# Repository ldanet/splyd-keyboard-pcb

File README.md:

# Splyd Keyboard PCB

Kicad files for my custom split ergo keyboard PCB.

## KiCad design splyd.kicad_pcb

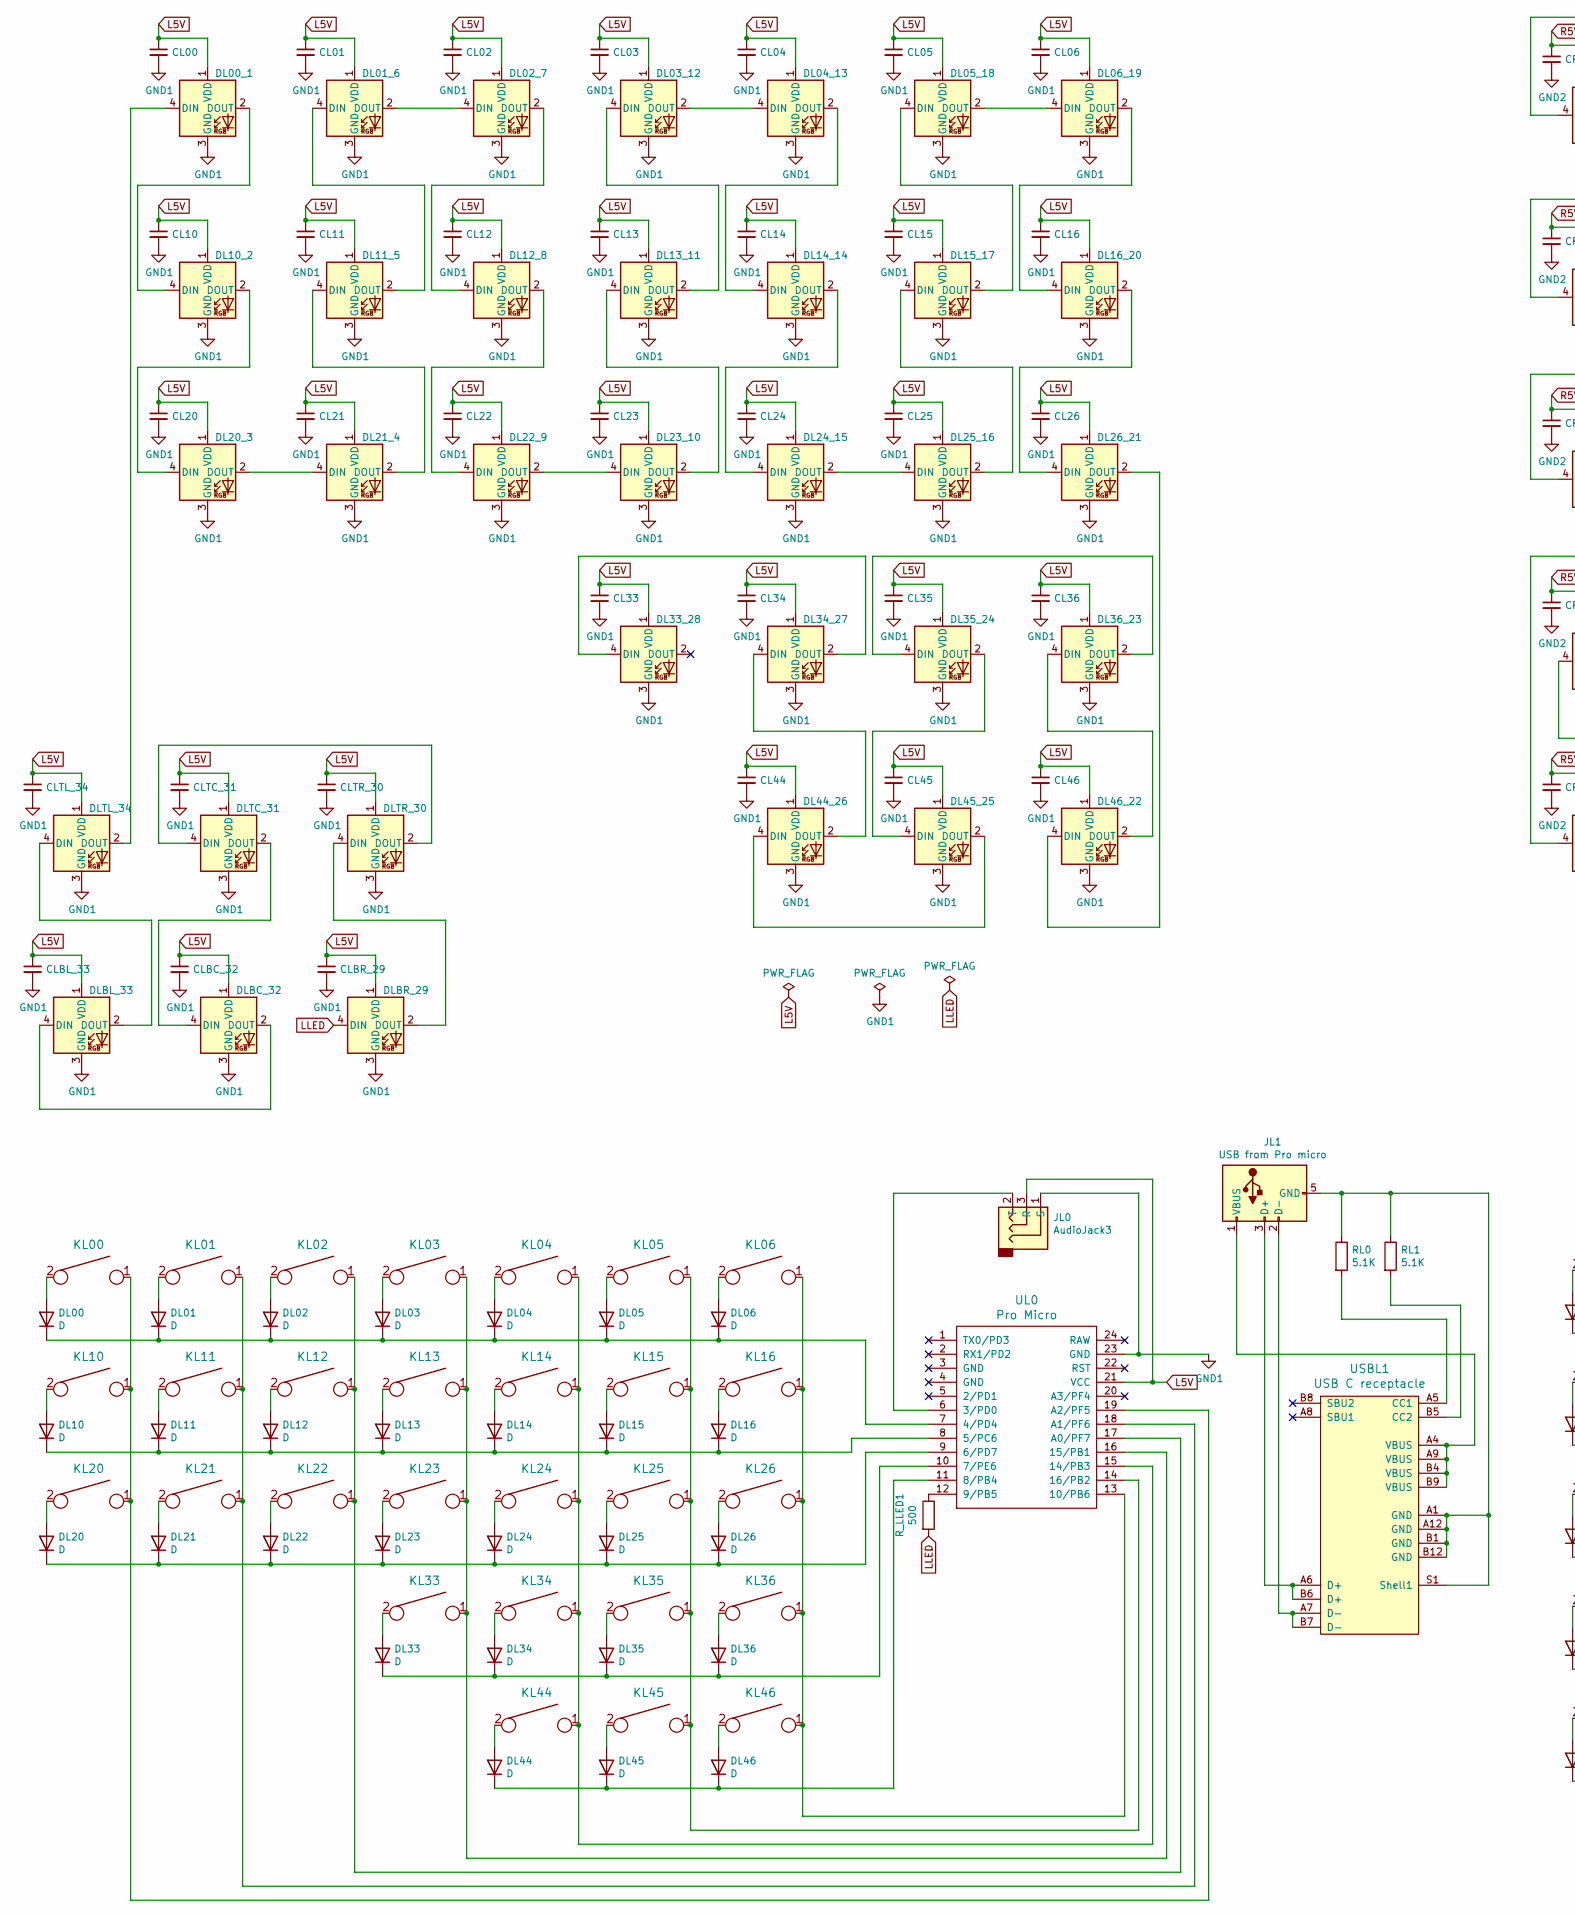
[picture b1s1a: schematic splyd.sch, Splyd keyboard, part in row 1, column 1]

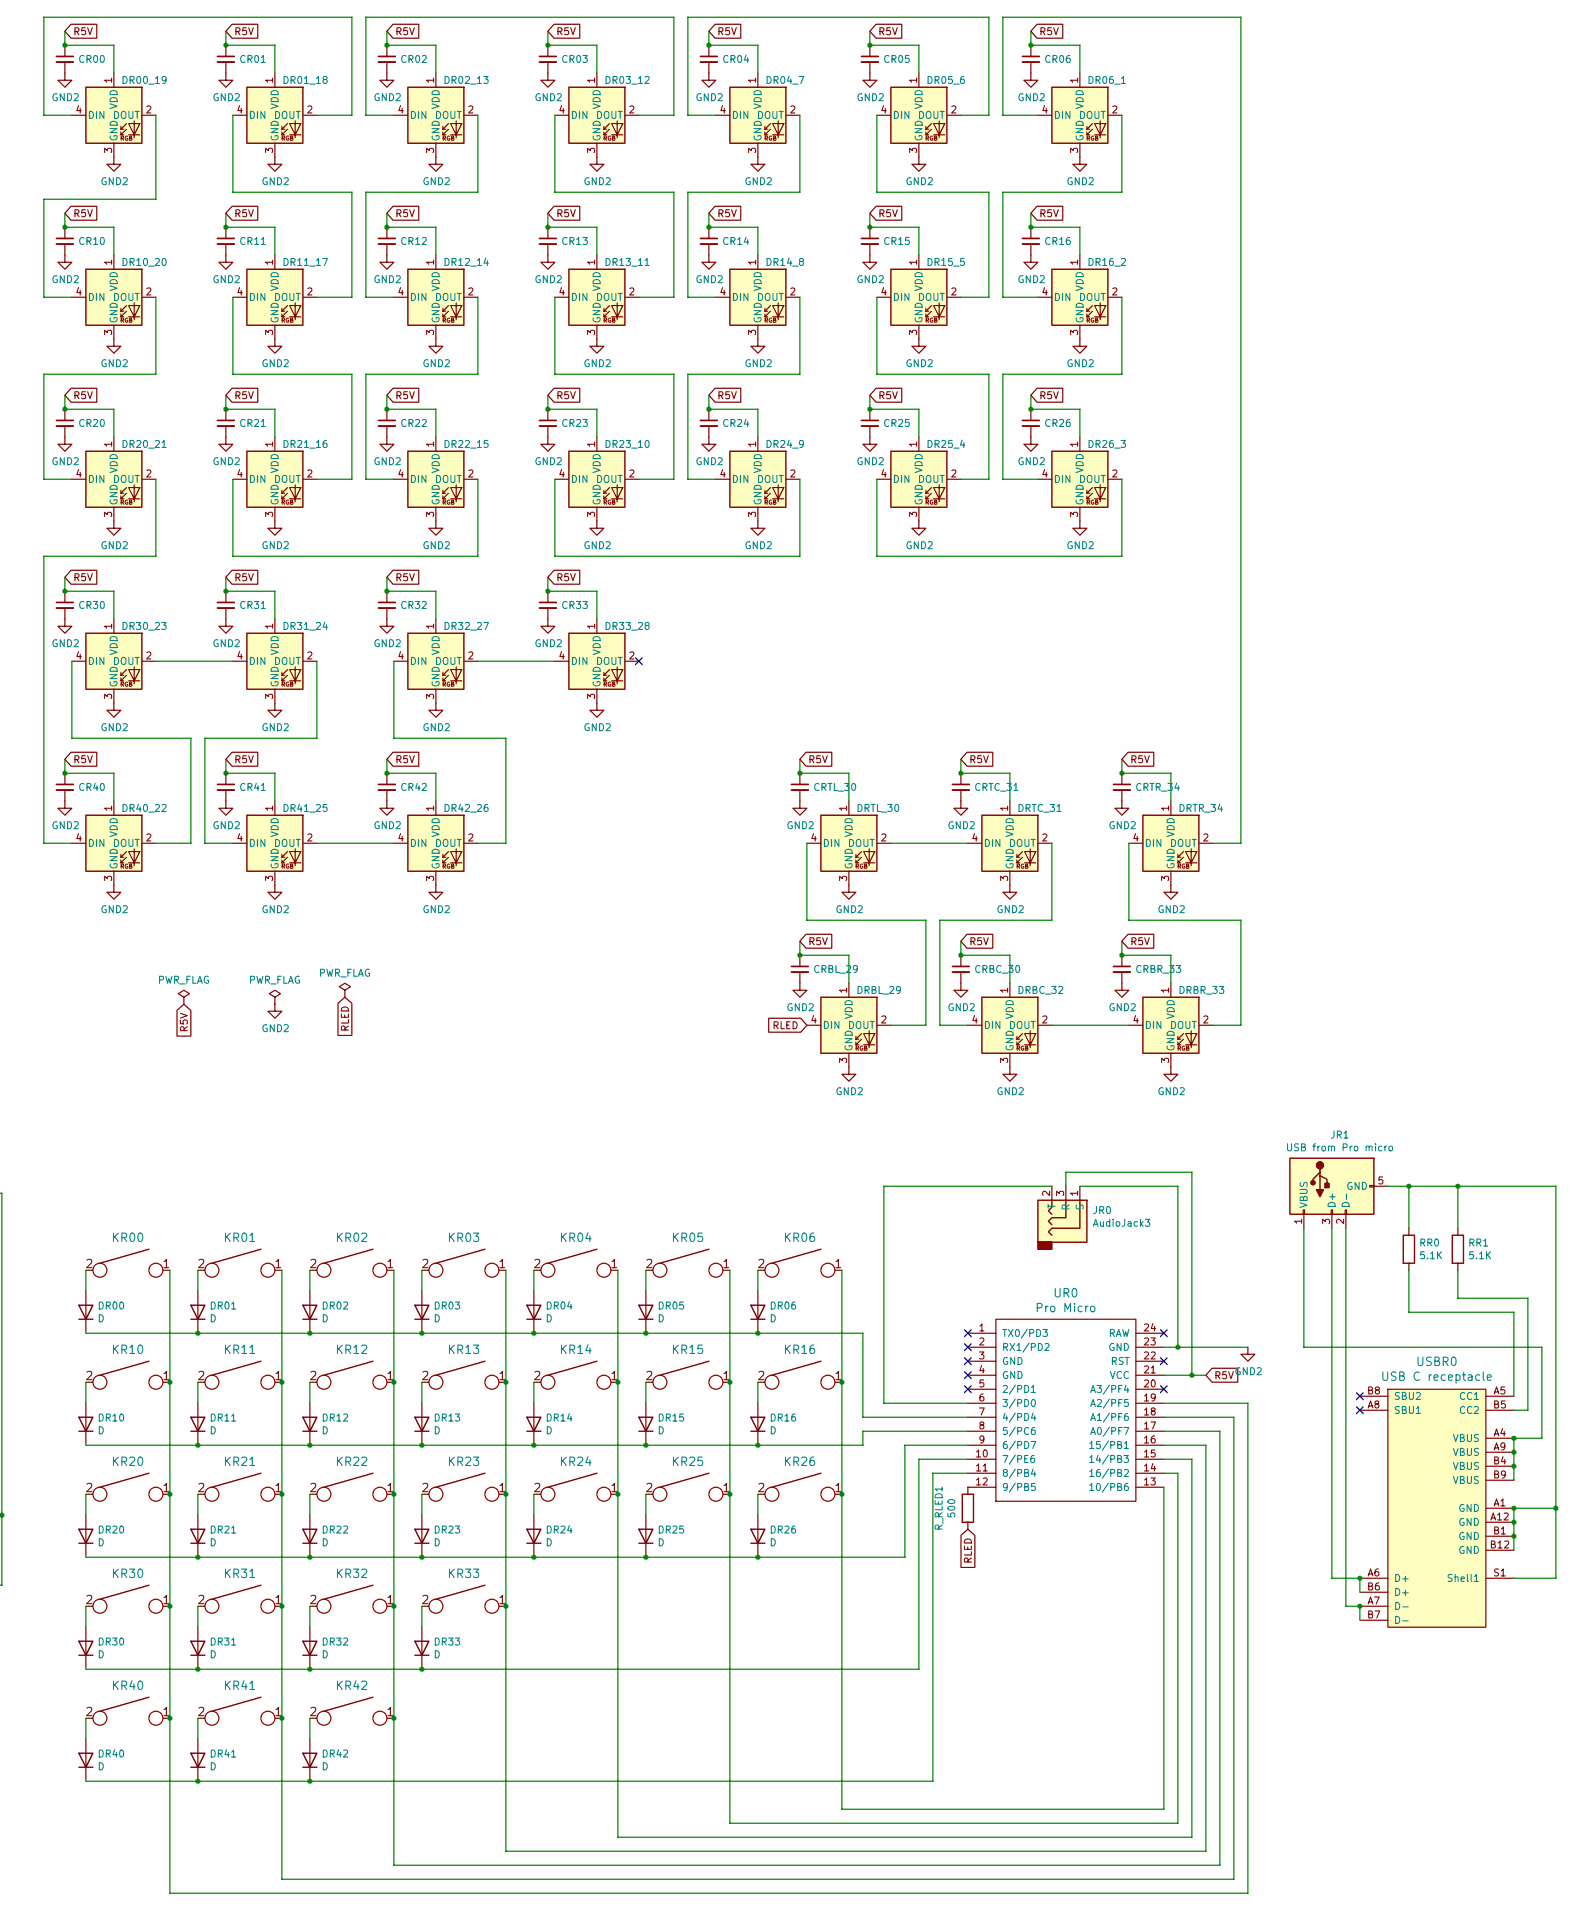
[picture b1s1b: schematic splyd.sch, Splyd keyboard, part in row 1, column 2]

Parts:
CL00, CL01, CL02, CL03, CL04, CL05, CL06, CL10, CL11, CL12, CL13, CL14, CL15, CL16, CL20, CL21, CL22, CL23, CL24, CL25, CL26, CL33, CL34, CL35, CL36, CL44, CL45, CL46: C_Small; C_0603_1608Metric_Pad1.05x0.95mm_HandSolder
CLBC_32: C_Small; C_0603_1608Metric_Pad1.05x0.95mm_HandSolder
CLBL_33: C_Small; C_0603_1608Metric_Pad1.05x0.95mm_HandSolder
CLBR_29: C_Small; C_0603_1608Metric_Pad1.05x0.95mm_HandSolder
CLTC_31: C_Small; C_0603_1608Metric_Pad1.05x0.95mm_HandSolder
CLTL_34: C_Small; C_0603_1608Metric_Pad1.05x0.95mm_HandSolder
CLTR_30: C_Small; C_0603_1608Metric_Pad1.05x0.95mm_HandSolder
CR00, CR01, CR02, CR03, CR04, CR05, CR06, CR10, CR11, CR12, CR13, CR14, CR15, CR16, CR20, CR21, CR22, CR23, CR24, CR25, CR26, CR30, CR31, CR32, CR33, CR40, CR41, CR42: C_Small; C_0603_1608Metric_Pad1.05x0.95mm_HandSolder
CRBC_30: C_Small; C_0603_1608Metric_Pad1.05x0.95mm_HandSolder
CRBL_29: C_Small; C_0603_1608Metric_Pad1.05x0.95mm_HandSolder
CRBR_33: C_Small; C_0603_1608Metric_Pad1.05x0.95mm_HandSolder
CRTC_31: C_Small; C_0603_1608Metric_Pad1.05x0.95mm_HandSolder
CRTL_30: C_Small; C_0603_1608Metric_Pad1.05x0.95mm_HandSolder
CRTR_34: C_Small; C_0603_1608Metric_Pad1.05x0.95mm_HandSolder
DL00, DL01, DL02, DL03, DL04, DL05, DL06, DL10, DL11, DL12, DL13, DL14, DL15, DL16, DL20, DL21, DL22, DL23, DL24, DL25, DL26, DL33, DL34, DL35, DL36, DL44, DL45, DL46: D; D_SOD123_axial
DL00_1, DL01_6, DL02_7, DL03_12, DL04_13, DL05_18, DL06_19, DL10_2, DL11_5, DL12_8, DL13_11, DL14_14, DL15_17, DL16_20, DL20_3, DL21_4, DL22_9, DL23_10, DL24_15, DL25_16, DL26_21, DL33_28, DL34_27, DL35_24, DL36_23, DL44_26, DL45_25, DL46_22: SK6812MINI-E; SK6812MINIE-simple
DLBC_32: SK6812MINI-E; SK6812MINIE-simple_no-hole
DLBL_33: SK6812MINI-E; SK6812MINIE-simple_no-hole
DLBR_29: SK6812MINI-E; SK6812MINIE-simple_no-hole
DLTC_31: SK6812MINI-E; SK6812MINIE-simple_no-hole
DLTL_34: SK6812MINI-E; SK6812MINIE-simple_no-hole
DLTR_30: SK6812MINI-E; SK6812MINIE-simple_no-hole
DR00, DR01, DR02, DR03, DR04, DR05, DR06, DR10, DR11, DR12, DR13, DR14, DR15, DR16, DR20, DR21, DR22, DR23, DR24, DR25, DR26, DR30, DR31, DR32, DR33, DR40, DR41, DR42: D; D_SOD123_axial
DR00_19, DR01_18, DR02_13, DR03_12, DR04_7, DR05_6, DR06_1, DR10_20, DR11_17, DR12_14, DR13_11, DR14_8, DR15_5, DR16_2, DR20_21, DR21_16, DR22_15, DR23_10, DR24_9, DR25_4, DR26_3, DR30_23, DR31_24, DR32_27, DR33_28, DR40_22, DR41_25, DR42_26: SK6812MINI-E; SK6812MINIE-simple
DRBC_32: SK6812MINI-E; SK6812MINIE-simple_no-hole
DRBL_29: SK6812MINI-E; SK6812MINIE-simple_no-hole
DRBR_33: SK6812MINI-E; SK6812MINIE-simple_no-hole
DRTC_31: SK6812MINI-E; SK6812MINIE-simple_no-hole
DRTL_30: SK6812MINI-E; SK6812MINIE-simple_no-hole
DRTR_34: SK6812MINI-E; SK6812MINIE-simple_no-hole
JL0: AudioJack3; TRS-PJ-320B
JL1: USB from Pro micro; Pad_1x04_SMD_1x2mm
JR0: AudioJack3; TRS-PJ-320B
JR1: USB from Pro micro; Pad_1x04_SMD_1x2mm
KL00, KL01, KL02, KL03, KL04, KL05, KL06, KL10, KL11, KL12, KL13, KL14, KL15, KL16, KL20, KL21, KL22, KL23, KL24, KL25, KL26, KL33, KL34, KL35, KL36, KL44, KL45, KL46: KEYSW; Kailh_socket_MX--space
KR00, KR01, KR02, KR03, KR04, KR05, KR06, KR10, KR11, KR12, KR13, KR14, KR15, KR16, KR20, KR21, KR22, KR23, KR24, KR25, KR26, KR30, KR31, KR32, KR33, KR40, KR41, KR42: KEYSW; Kailh_socket_MX--space
RL0, RL1: 5.1K; R_0603_1608Metric
RR0, RR1: 5.1K; R_0603_1608Metric
R_LLED1: 500; R_0603_1608Metric
R_RLED1: 500; R_0603_1608Metric
UL0: Pro Micro; ArduinoProMicro-ZigZag
UR0: Pro Micro; ArduinoProMicro-ZigZag
USBL1: USB C receptacle; USB_C_GCT_USB4085
USBR0: USB C receptacle; USB_C_GCT_USB4085

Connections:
GND1: CL00.2, CL01.2, CL02.2, CL03.2, CL04.2, CL05.2, CL06.2, CL10.2, CL11.2, CL12.2, CL13.2, CL14.2, CL15.2, CL16.2, CL20.2, CL21.2, CL22.2, CL23.2, CL24.2, CL25.2, CL26.2, CL33.2, CL34.2, CL35.2, CL36.2, CL44.2, CL45.2, CL46.2, CLBC_32.2, CLBL_33.2, CLBR_29.2, CLTC_31.2, CLTL_34.2, CLTR_30.2, DL00_1.3 (GND), DL01_6.3 (GND), DL02_7.3 (GND), DL03_12.3 (GND), DL04_13.3 (GND), DL05_18.3 (GND), DL06_19.3 (GND), DL10_2.3 (GND), DL11_5.3 (GND), DL12_8.3 (GND), DL13_11.3 (GND), DL14_14.3 (GND), DL15_17.3 (GND), DL16_20.3 (GND), DL20_3.3 (GND), DL21_4.3 (GND), DL22_9.3 (GND), DL23_10.3 (GND), DL24_15.3 (GND), DL25_16.3 (GND), DL26_21.3 (GND), DL33_28.3 (GND), DL34_27.3 (GND), DL35_24.3 (GND), DL36_23.3 (GND), DL44_26.3 (GND), DL45_25.3 (GND), DL46_22.3 (GND), DLBC_32.3 (GND), DLBL_33.3 (GND), DLBR_29.3 (GND), DLTC_31.3 (GND), DLTL_34.3 (GND), DLTR_30.3 (GND), JL0.1 (S), UL0.23 (GND)
GND2: CR00.2, CR01.2, CR02.2, CR03.2, CR04.2, CR05.2, CR06.2, CR10.2, CR11.2, CR12.2, CR13.2, CR14.2, CR15.2, CR16.2, CR20.2, CR21.2, CR22.2, CR23.2, CR24.2, CR25.2, CR26.2, CR30.2, CR31.2, CR32.2, CR33.2, CR40.2, CR41.2, CR42.2, CRBC_30.2, CRBL_29.2, CRBR_33.2, CRTC_31.2, CRTL_30.2, CRTR_34.2, DR00_19.3 (GND), DR01_18.3 (GND), DR02_13.3 (GND), DR03_12.3 (GND), DR04_7.3 (GND), DR05_6.3 (GND), DR06_1.3 (GND), DR10_20.3 (GND), DR11_17.3 (GND), DR12_14.3 (GND), DR13_11.3 (GND), DR14_8.3 (GND), DR15_5.3 (GND), DR16_2.3 (GND), DR20_21.3 (GND), DR21_16.3 (GND), DR22_15.3 (GND), DR23_10.3 (GND), DR24_9.3 (GND), DR25_4.3 (GND), DR26_3.3 (GND), DR30_23.3 (GND), DR31_24.3 (GND), DR32_27.3 (GND), DR33_28.3 (GND), DR40_22.3 (GND), DR41_25.3 (GND), DR42_26.3 (GND), DRBC_32.3 (GND), DRBL_29.3 (GND), DRBR_33.3 (GND), DRTC_31.3 (GND), DRTL_30.3 (GND), DRTR_34.3 (GND), JR0.1 (S), UR0.23 (GND)
L5V: CL00.1, CL01.1, CL02.1, CL03.1, CL04.1, CL05.1, CL06.1, CL10.1, CL11.1, CL12.1, CL13.1, CL14.1, CL15.1, CL16.1, CL20.1, CL21.1, CL22.1, CL23.1, CL24.1, CL25.1, CL26.1, CL33.1, CL34.1, CL35.1, CL36.1, CL44.1, CL45.1, CL46.1, CLBC_32.1, CLBL_33.1, CLBR_29.1, CLTC_31.1, CLTL_34.1, CLTR_30.1, DL00_1.1 (VDD), DL01_6.1 (VDD), DL02_7.1 (VDD), DL03_12.1 (VDD), DL04_13.1 (VDD), DL05_18.1 (VDD), DL06_19.1 (VDD), DL10_2.1 (VDD), DL11_5.1 (VDD), DL12_8.1 (VDD), DL13_11.1 (VDD), DL14_14.1 (VDD), DL15_17.1 (VDD), DL16_20.1 (VDD), DL20_3.1 (VDD), DL21_4.1 (VDD), DL22_9.1 (VDD), DL23_10.1 (VDD), DL24_15.1 (VDD), DL25_16.1 (VDD), DL26_21.1 (VDD), DL33_28.1 (VDD), DL34_27.1 (VDD), DL35_24.1 (VDD), DL36_23.1 (VDD), DL44_26.1 (VDD), DL45_25.1 (VDD), DL46_22.1 (VDD), DLBC_32.1 (VDD), DLBL_33.1 (VDD), DLBR_29.1 (VDD), DLTC_31.1 (VDD), DLTL_34.1 (VDD), DLTR_30.1 (VDD), JL0.3 (R), UL0.21 (VCC)
LLED: DLBR_29.4 (DIN), R_LLED1.2
unnamed: DL00.1 (K), DL01.1 (K), DL02.1 (K), DL03.1 (K), DL04.1 (K), DL05.1 (K), DL06.1 (K), UL0.7 (4/PD4)
unnamed: DL00.2 (A), KL00.2
unnamed: DL00_1.2 (DOUT), DL10_2.4 (DIN)
unnamed: DL00_1.4 (DIN), DLTL_34.2 (DOUT)
unnamed: DL01.2 (A), KL01.2
unnamed: DL01_6.2 (DOUT), DL02_7.4 (DIN)
unnamed: DL01_6.4 (DIN), DL11_5.2 (DOUT)
unnamed: DL02.2 (A), KL02.2
unnamed: DL02_7.2 (DOUT), DL12_8.4 (DIN)
unnamed: DL03.2 (A), KL03.2
unnamed: DL03_12.2 (DOUT), DL04_13.4 (DIN)
unnamed: DL03_12.4 (DIN), DL13_11.2 (DOUT)
unnamed: DL04.2 (A), KL04.2
unnamed: DL04_13.2 (DOUT), DL14_14.4 (DIN)
unnamed: DL05.2 (A), KL05.2
unnamed: DL05_18.2 (DOUT), DL06_19.4 (DIN)
unnamed: DL05_18.4 (DIN), DL15_17.2 (DOUT)
unnamed: DL06.2 (A), KL06.2
unnamed: DL06_19.2 (DOUT), DL16_20.4 (DIN)
unnamed: DL10.1 (K), DL11.1 (K), DL12.1 (K), DL13.1 (K), DL14.1 (K), DL15.1 (K), DL16.1 (K), UL0.8 (5/PC6)
unnamed: DL10.2 (A), KL10.2
unnamed: DL10_2.2 (DOUT), DL20_3.4 (DIN)
unnamed: DL11.2 (A), KL11.2
unnamed: DL11_5.4 (DIN), DL21_4.2 (DOUT)
unnamed: DL12.2 (A), KL12.2
unnamed: DL12_8.2 (DOUT), DL22_9.4 (DIN)
unnamed: DL13.2 (A), KL13.2
unnamed: DL13_11.4 (DIN), DL23_10.2 (DOUT)
unnamed: DL14.2 (A), KL14.2
unnamed: DL14_14.2 (DOUT), DL24_15.4 (DIN)
unnamed: DL15.2 (A), KL15.2
unnamed: DL15_17.4 (DIN), DL25_16.2 (DOUT)
unnamed: DL16.2 (A), KL16.2
unnamed: DL16_20.2 (DOUT), DL26_21.4 (DIN)
unnamed: DL20.1 (K), DL21.1 (K), DL22.1 (K), DL23.1 (K), DL24.1 (K), DL25.1 (K), DL26.1 (K), UL0.9 (6/PD7)
unnamed: DL20.2 (A), KL20.2
unnamed: DL20_3.2 (DOUT), DL21_4.4 (DIN)
unnamed: DL21.2 (A), KL21.2
unnamed: DL22.2 (A), KL22.2
unnamed: DL22_9.2 (DOUT), DL23_10.4 (DIN)
unnamed: DL23.2 (A), KL23.2
unnamed: DL24.2 (A), KL24.2
unnamed: DL24_15.2 (DOUT), DL25_16.4 (DIN)
unnamed: DL25.2 (A), KL25.2
unnamed: DL26.2 (A), KL26.2
unnamed: DL26_21.2 (DOUT), DL46_22.4 (DIN)
unnamed: DL33.1 (K), DL34.1 (K), DL35.1 (K), DL36.1 (K), UL0.10 (7/PE6)
unnamed: DL33.2 (A), KL33.2
unnamed: DL33_28.4 (DIN), DL34_27.2 (DOUT)
unnamed: DL34.2 (A), KL34.2
unnamed: DL34_27.4 (DIN), DL44_26.2 (DOUT)
unnamed: DL35.2 (A), KL35.2
unnamed: DL35_24.2 (DOUT), DL45_25.4 (DIN)
unnamed: DL35_24.4 (DIN), DL36_23.2 (DOUT)
unnamed: DL36.2 (A), KL36.2
unnamed: DL36_23.4 (DIN), DL46_22.2 (DOUT)
unnamed: DL44.1 (K), DL45.1 (K), DL46.1 (K), UL0.11 (8/PB4)
unnamed: DL44.2 (A), KL44.2
unnamed: DL44_26.4 (DIN), DL45_25.2 (DOUT)
unnamed: DL45.2 (A), KL45.2
unnamed: DL46.2 (A), KL46.2
unnamed: DLBC_32.2 (DOUT), DLBL_33.4 (DIN)
unnamed: DLBC_32.4 (DIN), DLTC_31.2 (DOUT)
unnamed: DLBL_33.2 (DOUT), DLTL_34.4 (DIN)
unnamed: DLBR_29.2 (DOUT), DLTR_30.4 (DIN)
unnamed: DLTC_31.4 (DIN), DLTR_30.2 (DOUT)
unnamed: DR00.1 (K), DR01.1 (K), DR02.1 (K), DR03.1 (K), DR04.1 (K), DR05.1 (K), DR06.1 (K), UR0.7 (4/PD4)
unnamed: DR00.2 (A), KR00.2
unnamed: DR00_19.2 (DOUT), DR10_20.4 (DIN)
unnamed: DR00_19.4 (DIN), DR01_18.2 (DOUT)
unnamed: DR01.2 (A), KR01.2
unnamed: DR01_18.4 (DIN), DR11_17.2 (DOUT)
unnamed: DR02.2 (A), KR02.2
unnamed: DR02_13.2 (DOUT), DR12_14.4 (DIN)
unnamed: DR02_13.4 (DIN), DR03_12.2 (DOUT)
unnamed: DR03.2 (A), KR03.2
unnamed: DR03_12.4 (DIN), DR13_11.2 (DOUT)
unnamed: DR04.2 (A), KR04.2
unnamed: DR04_7.2 (DOUT), DR14_8.4 (DIN)
unnamed: DR04_7.4 (DIN), DR05_6.2 (DOUT)
unnamed: DR05.2 (A), KR05.2
unnamed: DR05_6.4 (DIN), DR15_5.2 (DOUT)
unnamed: DR06.2 (A), KR06.2
unnamed: DR06_1.2 (DOUT), DR16_2.4 (DIN)
unnamed: DR06_1.4 (DIN), DRTR_34.2 (DOUT)
unnamed: DR10.1 (K), DR11.1 (K), DR12.1 (K), DR13.1 (K), DR14.1 (K), DR15.1 (K), DR16.1 (K), UR0.8 (5/PC6)
unnamed: DR10.2 (A), KR10.2
unnamed: DR10_20.2 (DOUT), DR20_21.4 (DIN)
unnamed: DR11.2 (A), KR11.2
unnamed: DR11_17.4 (DIN), DR21_16.2 (DOUT)
unnamed: DR12.2 (A), KR12.2
unnamed: DR12_14.2 (DOUT), DR22_15.4 (DIN)
unnamed: DR13.2 (A), KR13.2
unnamed: DR13_11.4 (DIN), DR23_10.2 (DOUT)
unnamed: DR14.2 (A), KR14.2
unnamed: DR14_8.2 (DOUT), DR24_9.4 (DIN)
unnamed: DR15.2 (A), KR15.2
unnamed: DR15_5.4 (DIN), DR25_4.2 (DOUT)
unnamed: DR16.2 (A), KR16.2
unnamed: DR16_2.2 (DOUT), DR26_3.4 (DIN)
unnamed: DR20.1 (K), DR21.1 (K), DR22.1 (K), DR23.1 (K), DR24.1 (K), DR25.1 (K), DR26.1 (K), UR0.9 (6/PD7)
unnamed: DR20.2 (A), KR20.2
unnamed: DR20_21.2 (DOUT), DR40_22.4 (DIN)
unnamed: DR21.2 (A), KR21.2
unnamed: DR21_16.4 (DIN), DR22_15.2 (DOUT)
unnamed: DR22.2 (A), KR22.2
unnamed: DR23.2 (A), KR23.2
unnamed: DR23_10.4 (DIN), DR24_9.2 (DOUT)
unnamed: DR24.2 (A), KR24.2
unnamed: DR25.2 (A), KR25.2
unnamed: DR25_4.4 (DIN), DR26_3.2 (DOUT)
unnamed: DR26.2 (A), KR26.2
unnamed: DR30.1 (K), DR31.1 (K), DR32.1 (K), DR33.1 (K), UR0.10 (7/PE6)
unnamed: DR30.2 (A), KR30.2
unnamed: DR30_23.2 (DOUT), DR31_24.4 (DIN)
unnamed: DR30_23.4 (DIN), DR40_22.2 (DOUT)
unnamed: DR31.2 (A), KR31.2
unnamed: DR31_24.2 (DOUT), DR41_25.4 (DIN)
unnamed: DR32.2 (A), KR32.2
unnamed: DR32_27.2 (DOUT), DR33_28.4 (DIN)
unnamed: DR32_27.4 (DIN), DR42_26.2 (DOUT)
unnamed: DR33.2 (A), KR33.2
unnamed: DR40.1 (K), DR41.1 (K), DR42.1 (K), UR0.11 (8/PB4)
unnamed: DR40.2 (A), KR40.2
unnamed: DR41.2 (A), KR41.2
unnamed: DR41_25.2 (DOUT), DR42_26.4 (DIN)
unnamed: DR42.2 (A), KR42.2
unnamed: DRBC_32.2 (DOUT), DRBR_33.4 (DIN)
unnamed: DRBC_32.4 (DIN), DRTC_31.2 (DOUT)
unnamed: DRBL_29.2 (DOUT), DRTL_30.4 (DIN)
unnamed: DRBR_33.2 (DOUT), DRTR_34.4 (DIN)
unnamed: DRTC_31.4 (DIN), DRTL_30.2 (DOUT)
unnamed: JL0.2 (T), UL0.6 (3/PD0)
unnamed: JL1.1 (VBUS), USBL1.A4 (VBUS), USBL1.A9 (VBUS), USBL1.B4 (VBUS), USBL1.B9 (VBUS)
unnamed: JL1.2 (D-), USBL1.A7 (D-), USBL1.B7 (D-)
unnamed: JL1.3 (D+), USBL1.A6 (D+), USBL1.B6 (D+)
unnamed: JL1.5 (GND), RL0.1, RL1.1, USBL1.A1 (GND), USBL1.A12 (GND), USBL1.B1 (GND), USBL1.B12 (GND), USBL1.S1 (Shell1)
unnamed: JR0.2 (T), UR0.6 (3/PD0)
unnamed: JR1.1 (VBUS), USBR0.A4 (VBUS), USBR0.A9 (VBUS), USBR0.B4 (VBUS), USBR0.B9 (VBUS)
unnamed: JR1.2 (D-), USBR0.A7 (D-), USBR0.B7 (D-)
unnamed: JR1.3 (D+), USBR0.A6 (D+), USBR0.B6 (D+)
unnamed: JR1.5 (GND), RR0.1, RR1.1, USBR0.A1 (GND), USBR0.A12 (GND), USBR0.B1 (GND), USBR0.B12 (GND), USBR0.S1 (Shell1)
unnamed: KL00.1, KL10.1, KL20.1, UL0.19 (A2/PF5)
unnamed: KL01.1, KL11.1, KL21.1, UL0.18 (A1/PF6)
unnamed: KL02.1, KL12.1, KL22.1, UL0.17 (A0/PF7)
unnamed: KL03.1, KL13.1, KL23.1, KL33.1, UL0.16 (15/PB1)
unnamed: KL04.1, KL14.1, KL24.1, KL34.1, KL44.1, UL0.15 (14/PB3)
unnamed: KL05.1, KL15.1, KL25.1, KL35.1, KL45.1, UL0.14 (16/PB2)
unnamed: KL06.1, KL16.1, KL26.1, KL36.1, KL46.1, UL0.13 (10/PB6)
unnamed: KR00.1, KR10.1, KR20.1, KR30.1, KR40.1, UR0.19 (A2/PF5)
unnamed: KR01.1, KR11.1, KR21.1, KR31.1, KR41.1, UR0.18 (A1/PF6)
unnamed: KR02.1, KR12.1, KR22.1, KR32.1, KR42.1, UR0.17 (A0/PF7)
unnamed: KR03.1, KR13.1, KR23.1, KR33.1, UR0.16 (15/PB1)
unnamed: KR04.1, KR14.1, KR24.1, UR0.15 (14/PB3)
unnamed: KR05.1, KR15.1, KR25.1, UR0.14 (16/PB2)
unnamed: KR06.1, KR16.1, KR26.1, UR0.13 (10/PB6)
unnamed: RL0.2, USBL1.A5 (CC1)
unnamed: RL1.2, USBL1.B5 (CC2)
unnamed: RR0.2, USBR0.A5 (CC1)
unnamed: RR1.2, USBR0.B5 (CC2)
unnamed: R_LLED1.1, UL0.12 (9/PB5)
unnamed: R_RLED1.1, UR0.12 (9/PB5)
R5V: CR00.1, CR01.1, CR02.1, CR03.1, CR04.1, CR05.1, CR06.1, CR10.1, CR11.1, CR12.1, CR13.1, CR14.1, CR15.1, CR16.1, CR20.1, CR21.1, CR22.1, CR23.1, CR24.1, CR25.1, CR26.1, CR30.1, CR31.1, CR32.1, CR33.1, CR40.1, CR41.1, CR42.1, CRBC_30.1, CRBL_29.1, CRBR_33.1, CRTC_31.1, CRTL_30.1, CRTR_34.1, DR00_19.1 (VDD), DR01_18.1 (VDD), DR02_13.1 (VDD), DR03_12.1 (VDD), DR04_7.1 (VDD), DR05_6.1 (VDD), DR06_1.1 (VDD), DR10_20.1 (VDD), DR11_17.1 (VDD), DR12_14.1 (VDD), DR13_11.1 (VDD), DR14_8.1 (VDD), DR15_5.1 (VDD), DR16_2.1 (VDD), DR20_21.1 (VDD), DR21_16.1 (VDD), DR22_15.1 (VDD), DR23_10.1 (VDD), DR24_9.1 (VDD), DR25_4.1 (VDD), DR26_3.1 (VDD), DR30_23.1 (VDD), DR31_24.1 (VDD), DR32_27.1 (VDD), DR33_28.1 (VDD), DR40_22.1 (VDD), DR41_25.1 (VDD), DR42_26.1 (VDD), DRBC_32.1 (VDD), DRBL_29.1 (VDD), DRBR_33.1 (VDD), DRTC_31.1 (VDD), DRTL_30.1 (VDD), DRTR_34.1 (VDD), JR0.3 (R), UR0.21 (VCC)
RLED: DRBL_29.4 (DIN), R_RLED1.2

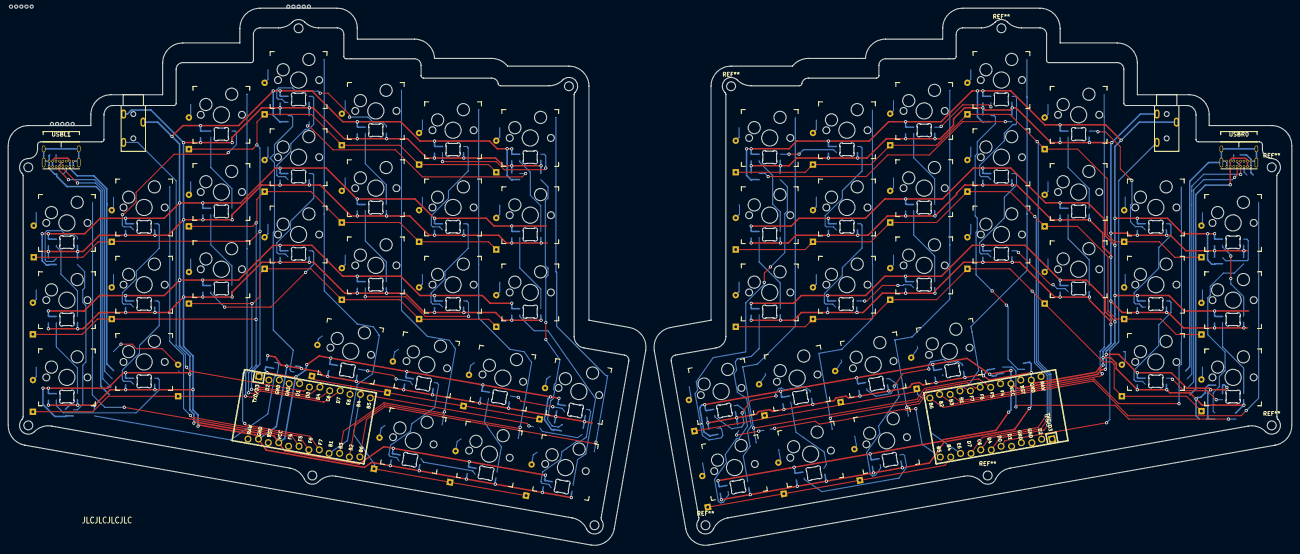
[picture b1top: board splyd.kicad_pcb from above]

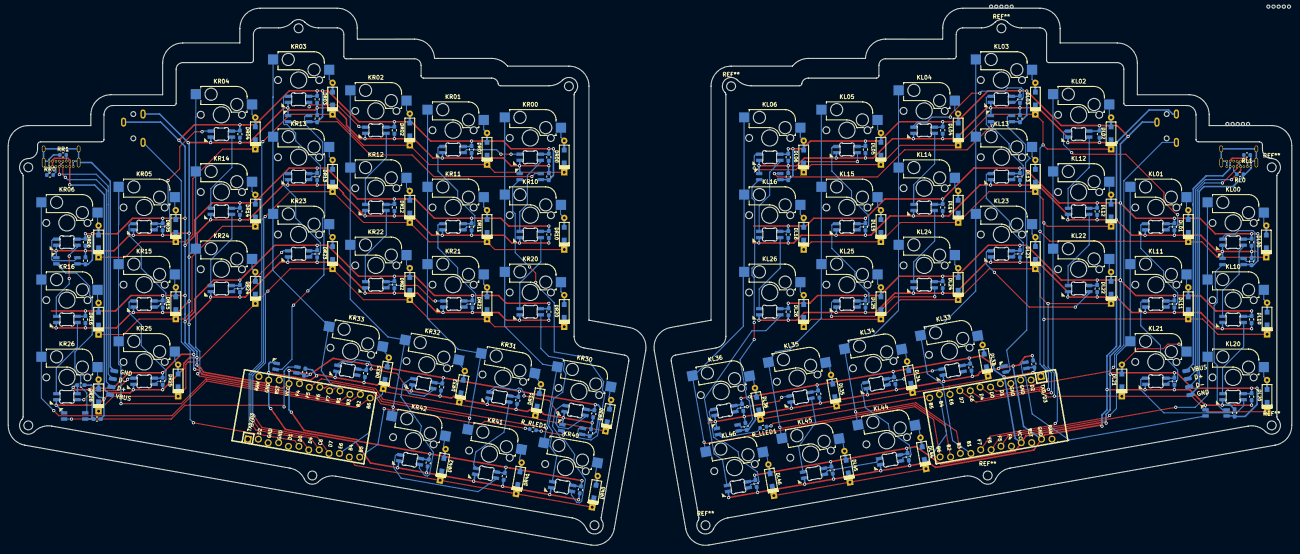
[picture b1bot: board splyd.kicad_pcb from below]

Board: 2 copper layers, 316.6 x 132.4 mm, 262 parts (134 on the bottom side), 168 nets.

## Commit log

2020-09-05 First commit, left hand mostly done
2020-09-05 Add right hand and prepare footprint placements
2020-09-05 Cleanup reference posisions on right hand silk
2020-09-06 Both halves fully wired
2020-09-27 Keyswitch footprint with window and 3rd time routing
2022-04-09 Wire key RGB diodes for right thumb cluster
2022-04-09 Fix SK6812MINI-E schema
2022-04-09 Wire key RGB diodes for right thumb cluster with proper pinouts
2022-04-09 Wire bottom left underglow LED on right hand
2022-04-11 Place all RGB LEDs
2022-04-13 Wire all LEDs on left thumb cluster
2022-04-14 Wire LED data to more suitable pin (shifts all row pins by 1)
2022-04-15 Wire all LEDs on right half
2022-04-15 Complete trace routing
2022-04-15 Fill ground planes and panelize
2022-04-24 Edge cut rework and prep for case design
2022-04-25 Fix edge cuts to work with 1mm mill bit and create case svg
2022-04-26 Add switch cutouts in switch plate
2022-04-27 Add remaining layers to case svg
